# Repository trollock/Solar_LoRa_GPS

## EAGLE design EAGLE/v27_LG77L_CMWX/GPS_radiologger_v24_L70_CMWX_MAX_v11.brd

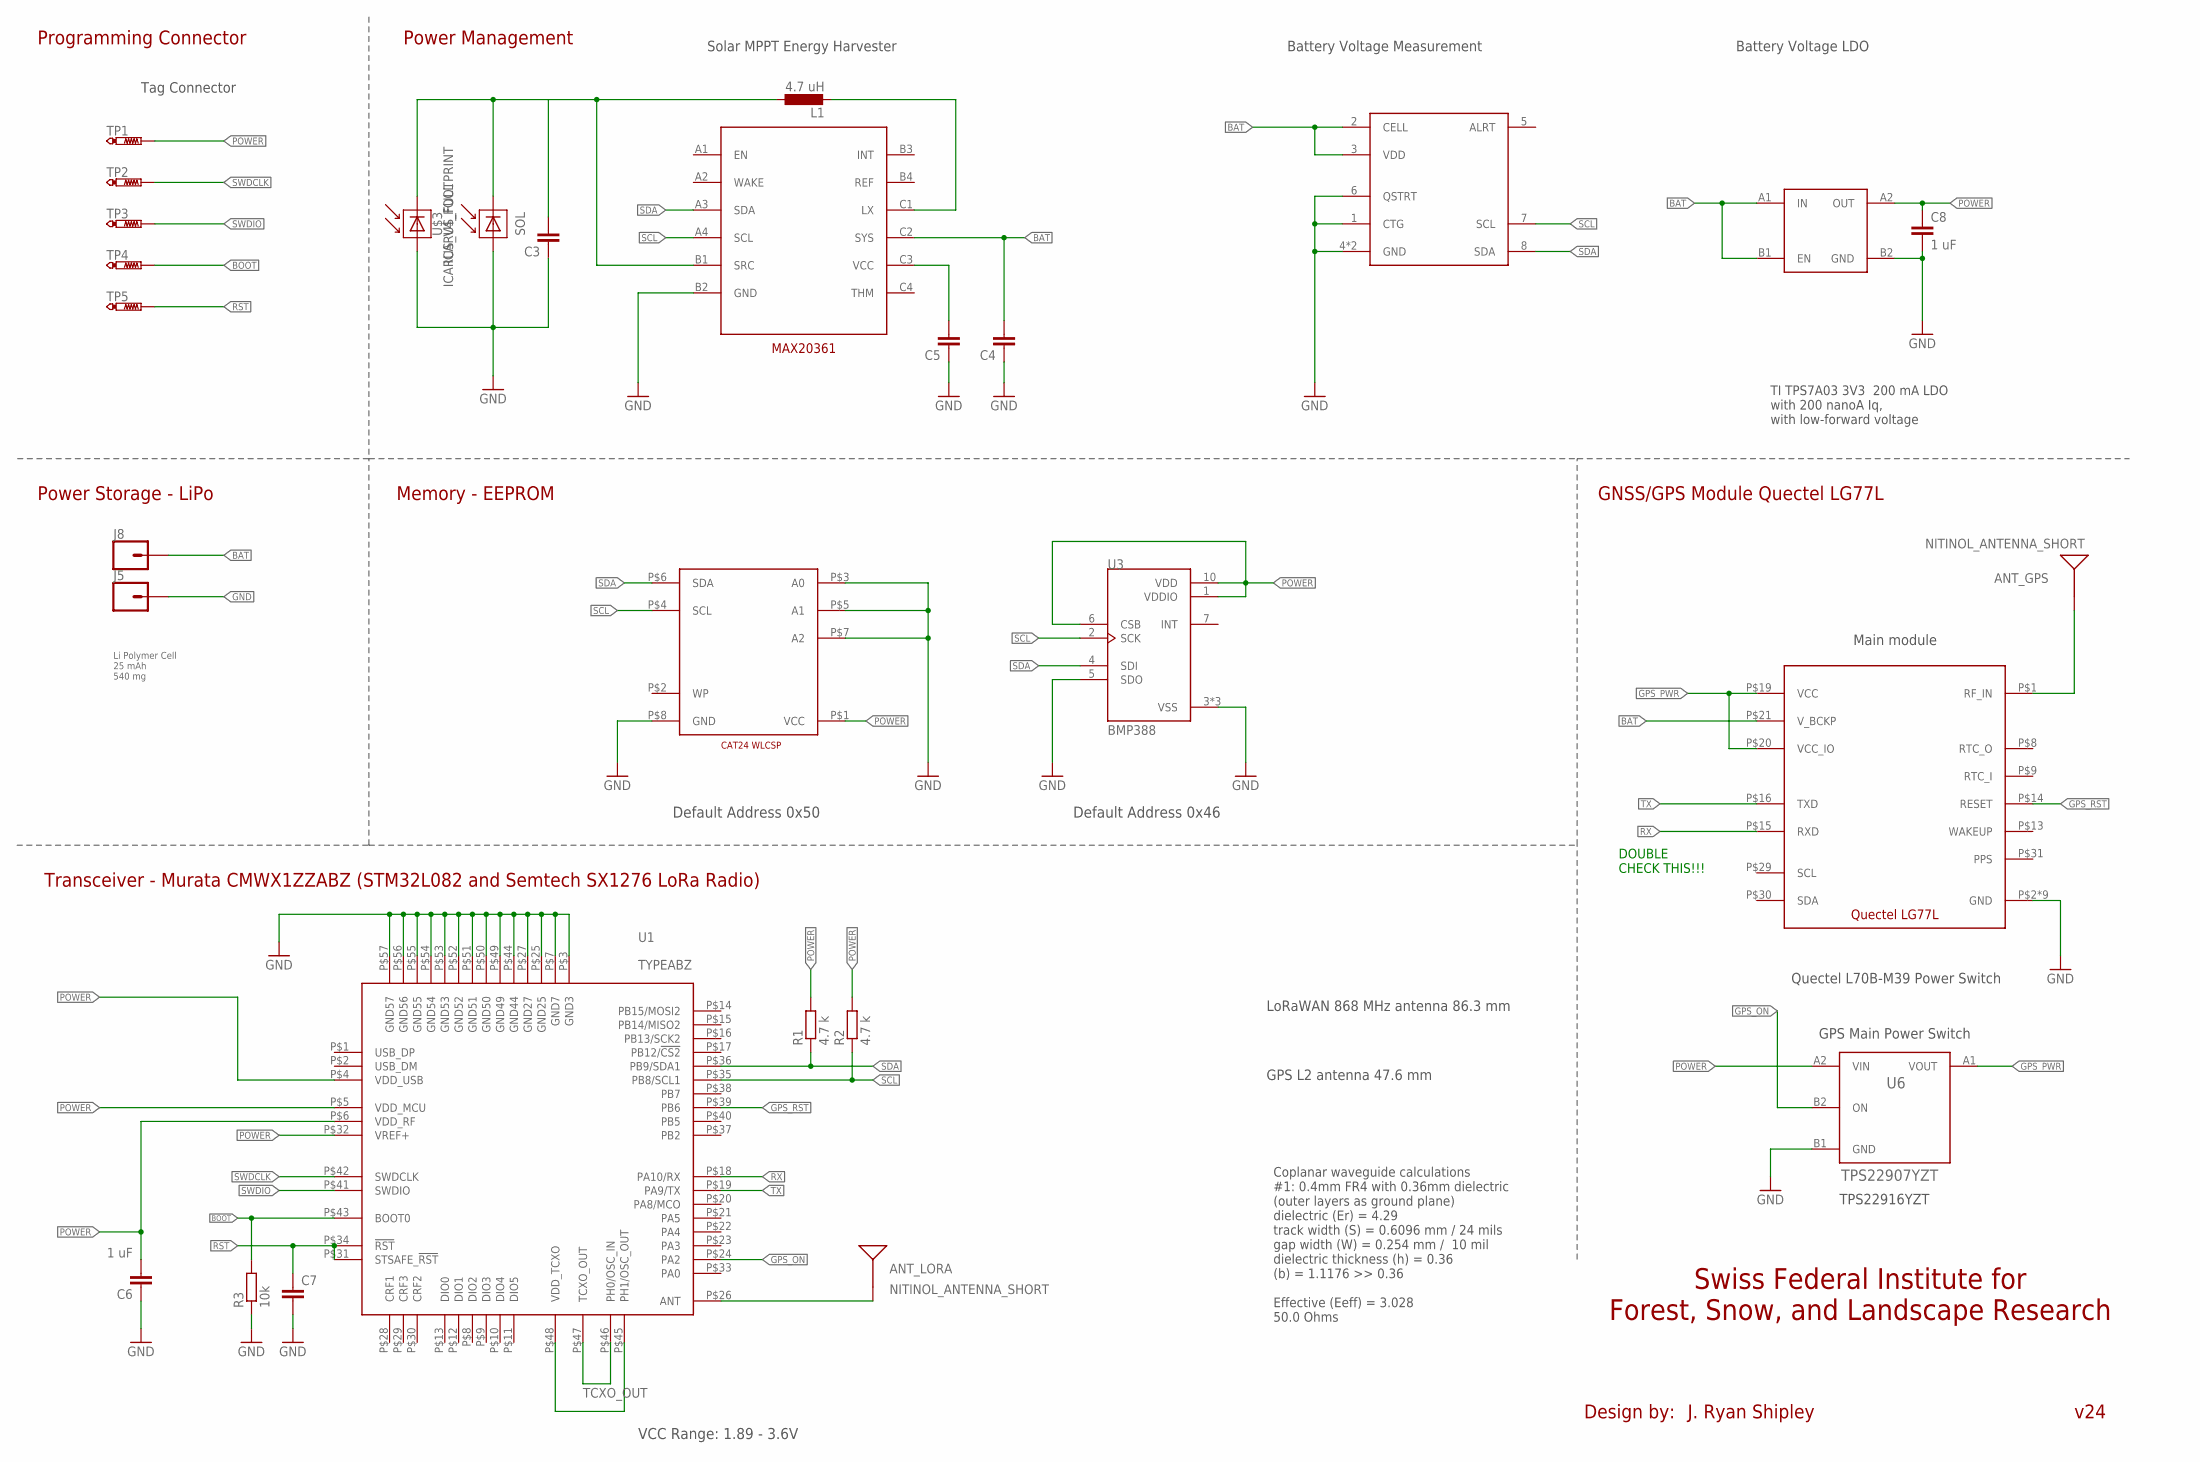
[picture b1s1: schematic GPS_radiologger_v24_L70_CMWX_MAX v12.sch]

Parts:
ANT_GPS: NITINOL_ANTENNA_SHORT; ICARUS_NITINOL_ANTENNA_SHORT
ANT_LORA: NITINOL_ANTENNA_SHORT; ICARUS_NITINOL_ANTENNA_SHORT
C3: 10UF; 0603-TIGHT
C4, C5: 1.0UF; 0402-TIGHTER
C6, C8: 1 uF; 0402-TIGHTER
C7: C-EUC0201; C0201
J5, J8: CONN_01PTH_NO_SILK_SMALL; 1X01_SMALL
L1: 4.7 uH; INDC2016X120L
R1, R2: 4.7 k; R0201
R3: 10k; R0201
SOL: ICARUS_V4_FOOTPRINT; ICARUS_FULL_FOOTPRINT
TP1, TP2, TP3, TP4, TP5: PTR1TP08SQ; TP08SQ
U1: TYPEABZ
U2: LG77L
U3: BMP388; PQFN50P200X200X80-10N
U4: TPS7A03-DSBGA; BGA4N35P2X2_70X70X40N
U5: MAX17048G+; SON50P200X200X75-9T80X120L
U6: TPS22907YZT; YFP0004-DSBGA
U7: CAT24_WLCSP8; WLCSP8
U8: MAX20361; BGA12N40P4X3_123X163X64N
U$3: ICARUS_FULL

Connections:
BAT: C4.P$2 (2), J8.P$1, U2.P$21 (V_BCKP), U4.A1 (IN), U4.B1 (EN), U5.2 (CELL), U5.3 (VDD), U8.C2 (SYS); also elsewhere on the board
BOOT: R3.2, TP4.TP, U1.P$43 (BOOT0)
GND: C3.P$1 (1), C4.P$1 (1), C5.P$1 (1), C6.P$1 (1), C7.2, C8.P$2 (2), J5.P$1, R3.1, SOL.P$2 (MINUS), U1.P$3 (GND3), U1.P$7 (GND7), U1.P$25 (GND25), U1.P$27 (GND27), U1.P$44 (GND44), U1.P$49 (GND49), U1.P$50 (GND50), U1.P$51 (GND51), U1.P$52 (GND52), U1.P$53 (GND53), U1.P$54 (GND54), U1.P$55 (GND55), U1.P$56 (GND56), U1.P$57 (GND57), U2.P$2 (GND), U3.3 (VSS), U3.5 (SDO), U3.8 (VSS), U3.9 (VSS), U4.B2 (GND), U5.1 (CTG), U5.4 (GND), U5.6 (QSTRT), U6.B1 (GND), U7.P$3 (A0), U7.P$5 (A1), U7.P$7 (A2), U7.P$8 (GND), U8.B2 (GND), U$3.P$2 (MINUS); also elsewhere on the board
GPS_ON: U1.P$24 (PA2), U6.B2 (ON)
GPS_PWR: U2.P$19 (VCC), U2.P$20 (VCC_IO), U6.A1 (VOUT); also elsewhere on the board
GPS_RST: U1.P$39 (PB6), U2.P$14 (RESET); also elsewhere on the board
unnamed: U1.P$45 (PH1/OSC_OUT), U1.P$48 (VDD_TCXO)
unnamed 7: ANT_GPS.1, ANT_GPS.2, ANT_GPS.3, U2.P$1 (RF_IN); also elsewhere on the board
unnamed: L1.2, U8.C1 (LX)
unnamed: C5.P$2 (2), U8.C3 (VCC)
unnamed: ANT_LORA.1, ANT_LORA.2, ANT_LORA.3, U1.P$26 (ANT)
unnamed: C3.P$2 (2), L1.1, SOL.P$1 (PLUS), U8.B1 (SRC), U$3.P$1 (PLUS)
POWER: C6.P$2 (2), C8.P$1 (1), R1.2, R2.2, TP1.TP, U1.P$4 (VDD_USB), U1.P$5 (VDD_MCU), U1.P$6 (VDD_RF), U1.P$32 (VREF+), U3.1 (VDDIO), U3.6 (CSB), U3.10 (VDD), U4.A2 (OUT), U6.A2 (VIN), U7.P$1 (VCC)
RST: C7.1, TP5.TP, U1.P$31 (STSAFE_!RST), U1.P$34 (!RST)
RX: U1.P$18 (PA10/RX), U2.P$15 (RXD); also elsewhere on the board
SCL: R2.1, U1.P$35 (PB8/SCL1), U3.2 (SCK), U5.7 (SCL), U7.P$4 (SCL), U8.A4 (SCL); also elsewhere on the board
SDA: R1.1, U1.P$36 (PB9/SDA1), U3.4 (SDI), U5.8 (SDA), U7.P$6 (SDA), U8.A3 (SDA); also elsewhere on the board
SWDCLK: TP2.TP, U1.P$42 (SWDCLK)
SWDIO: TP3.TP, U1.P$41 (SWDIO)
TCXO_OUT: U1.P$46 (PH0/OSC_IN), U1.P$47 (TCXO_OUT)
TX: U1.P$19 (PA9/TX), U2.P$16 (TXD); also elsewhere on the board

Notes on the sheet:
GNSS/GPS Module Quectel LG77L
VCC Range: 1.89 - 3.6V
Swiss Federal Institute for Forest, Snow, and Landscape Research
Transceiver - Murata CMWX1ZZABZ (STM32L082 and Semtech SX1276 LoRa Radio)
Programming Connector
Power Storage - LiPo
Design by:
J. Ryan Shipley
v24
Li Polymer Cell 25 mAh 540 mg
Power Management
Solar MPPT Energy Harvester
Memory - EEPROM
Main module
Coplanar waveguide calculations #1: 0.4mm FR4 with 0.36mm dielectric (outer layers as ground plane) dielectric (Er) = 4.29 track width (S) = 0.6096 mm / 24 mils gap width (W) = 0.254 mm / 10 mil dielectric thickness (h) = 0.36 (b) = 1.1176 >> 0.36 Effective (Eeff) = 3.028 50.0 Ohms
Tag Connector
Default Address 0x50
GPS Main Power Switch
TI TPS7A03 3V3 200 mA LDO with 200 nanoA Iq, with low-forward voltage
Quectel L70B-M39 Power Switch
Battery Voltage Measurement
Battery Voltage LDO
Default Address 0x46
TPS22916YZT
GPS L2 antenna 47.6 mm
LoRaWAN 868 MHz antenna 86.3 mm
DOUBLE CHECK THIS!!!

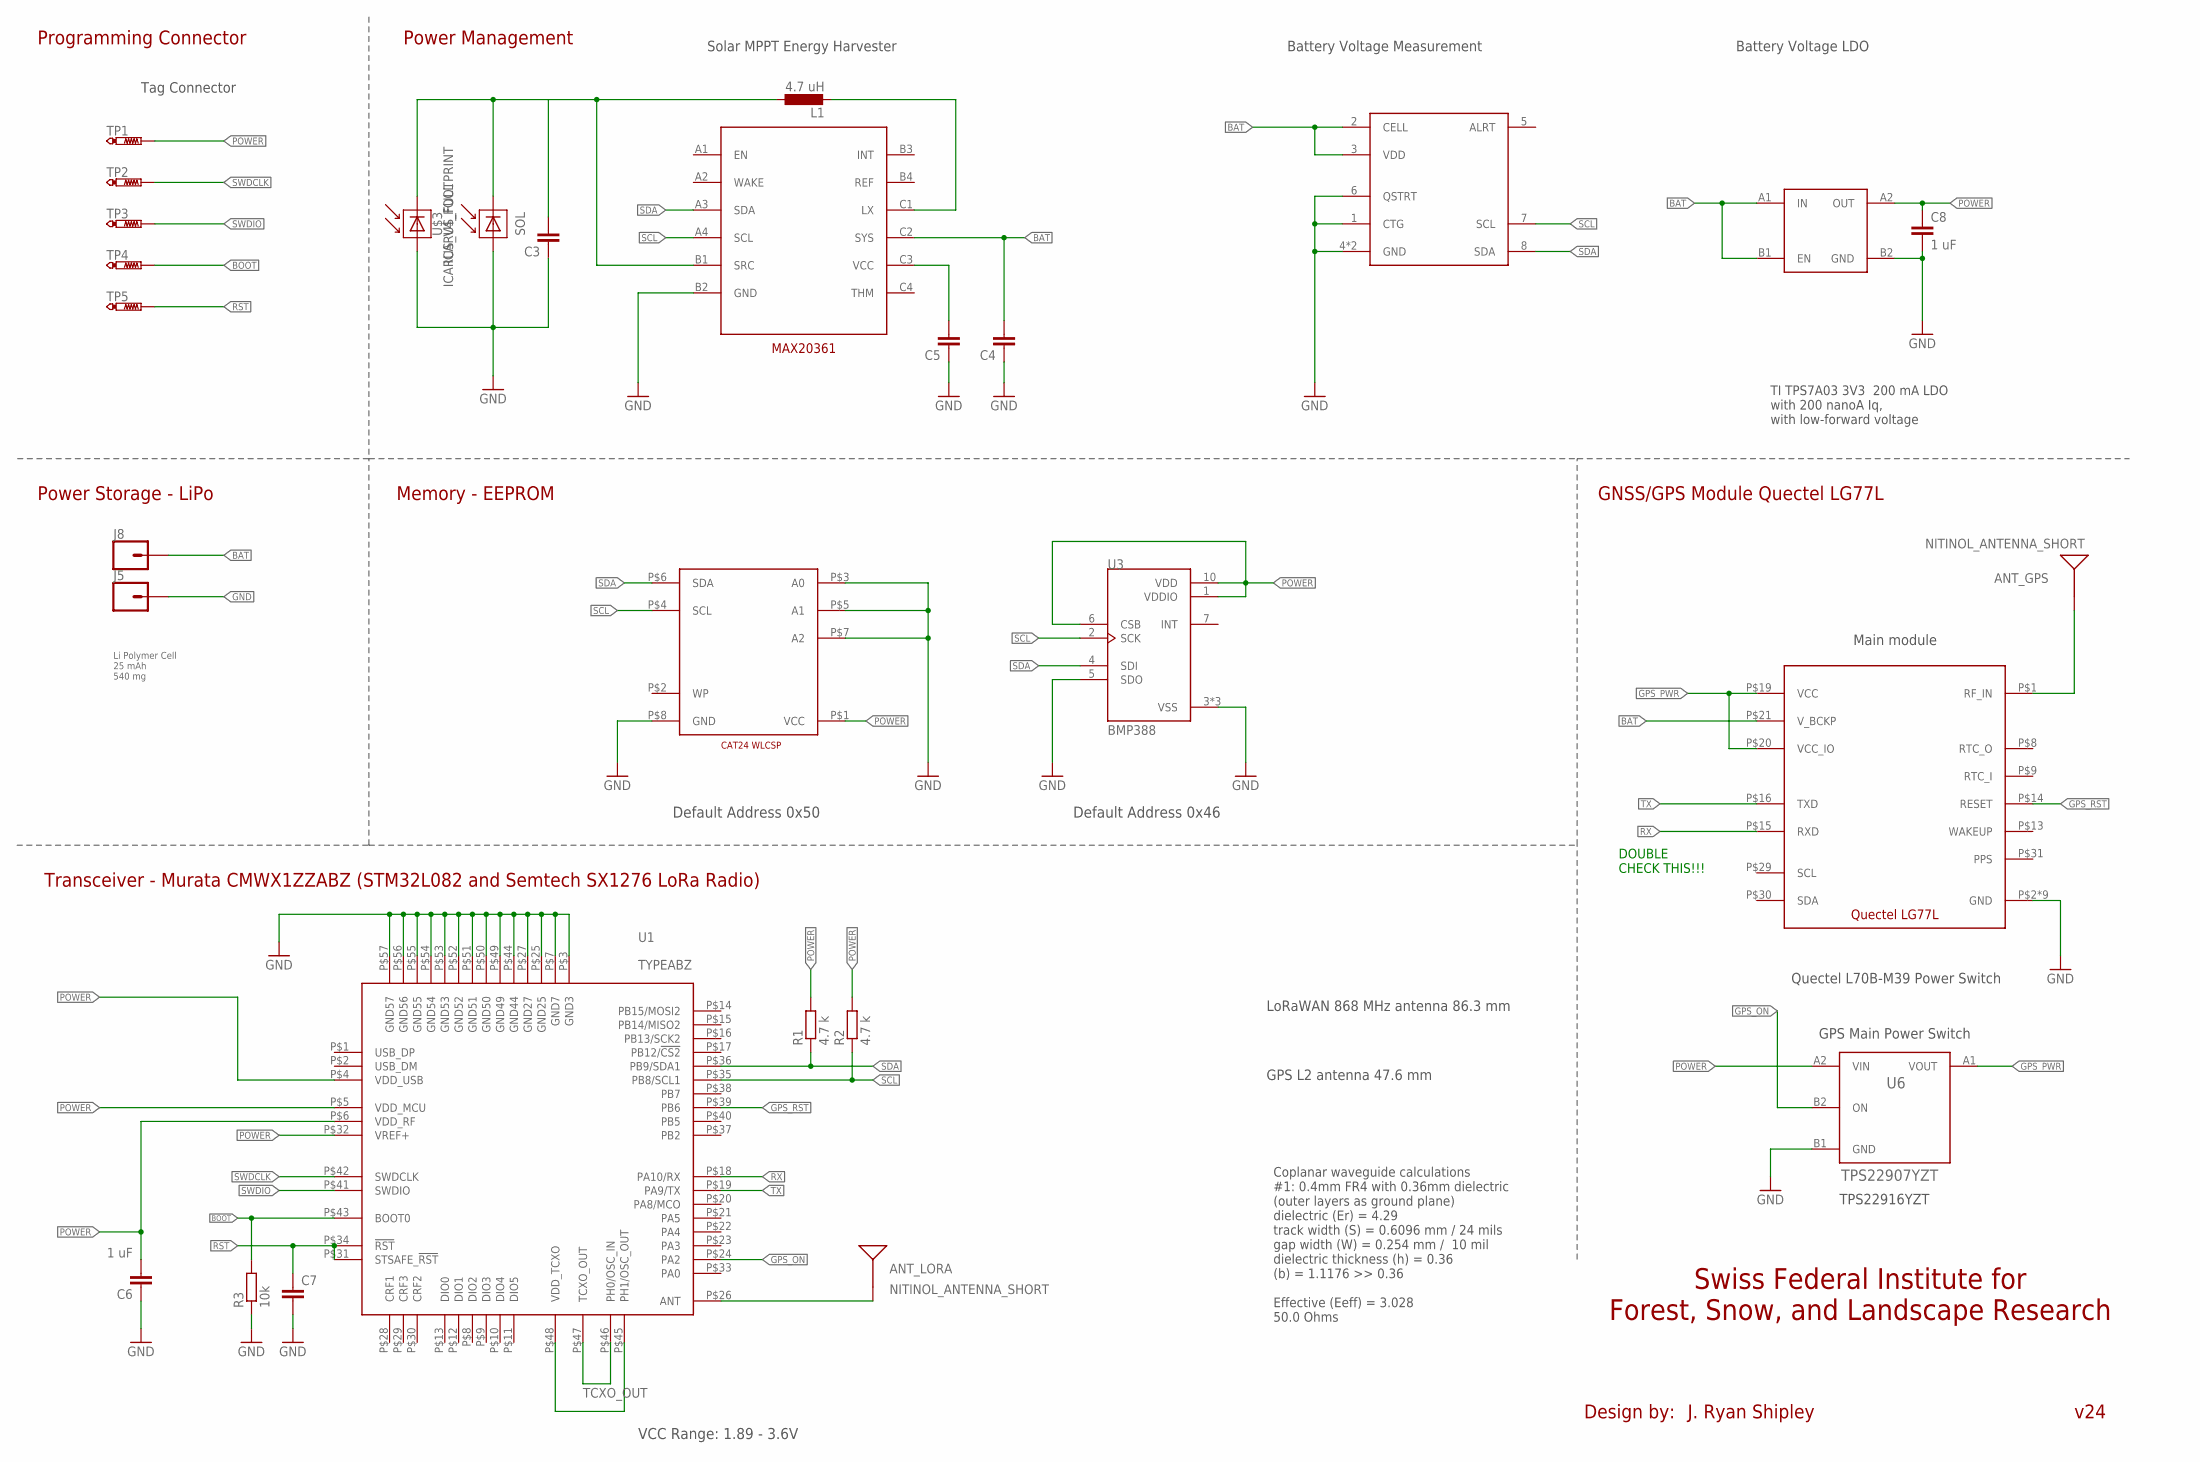
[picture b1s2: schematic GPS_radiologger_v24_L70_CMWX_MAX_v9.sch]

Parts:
ANT_GPS: NITINOL_ANTENNA_SHORT; ICARUS_NITINOL_ANTENNA_SHORT
ANT_LORA: NITINOL_ANTENNA_SHORT; ICARUS_NITINOL_ANTENNA_SHORT
C3: 10UF; 0603-TIGHT
C4, C5: 1.0UF; 0402-TIGHTER
C6, C8: 1 uF; 0402-TIGHTER
C7: C-EUC0201; C0201
J5, J8: CONN_01PTH_NO_SILK_SMALL; 1X01_SMALL
L1: 4.7 uH; INDC2016X120L
R1, R2: 4.7 k; R0201
R3: 10k; R0201
SOL: ICARUS_V4_FOOTPRINT; ICARUS_FULL_FOOTPRINT
TP1, TP2, TP3, TP4, TP5: PTR1TP08SQ; TP08SQ
U1: TYPEABZ
U3: BMP388; PQFN50P200X200X80-10N
U4: TPS7A03-DSBGA; BGA4N35P2X2_70X70X40N
U6: TPS22907YZT; YFP0004-DSBGA
U7: CAT24_WLCSP8; WLCSP8
U8: MAX20361; BGA12N40P4X3_123X163X64N
U$1: LG77L
U$2: MAX17048G+; SON50P200X200X75-9T80X120L
U$3: ICARUS_FULL

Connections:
BAT: C4.P$2 (2), J8.P$1, U4.A1 (IN), U4.B1 (EN), U8.C2 (SYS), U$1.P$21 (V_BCKP), U$2.2 (CELL), U$2.3 (VDD); also elsewhere on the board
BOOT: R3.2, TP4.TP, U1.P$43 (BOOT0)
GND: C3.P$1 (1), C4.P$1 (1), C5.P$1 (1), C6.P$1 (1), C7.2, C8.P$2 (2), J5.P$1, R3.1, SOL.P$2 (MINUS), U1.P$3 (GND3), U1.P$7 (GND7), U1.P$25 (GND25), U1.P$27 (GND27), U1.P$44 (GND44), U1.P$49 (GND49), U1.P$50 (GND50), U1.P$51 (GND51), U1.P$52 (GND52), U1.P$53 (GND53), U1.P$54 (GND54), U1.P$55 (GND55), U1.P$56 (GND56), U1.P$57 (GND57), U3.3 (VSS), U3.5 (SDO), U3.8 (VSS), U3.9 (VSS), U4.B2 (GND), U6.B1 (GND), U7.P$3 (A0), U7.P$5 (A1), U7.P$7 (A2), U7.P$8 (GND), U8.B2 (GND), U$1.P$2 (GND), U$1.P$18 (GND), U$1.P$37 (GND), U$1.P$38 (GND), U$1.P$39 (GND), U$1.P$40 (GND), U$1.P$41 (GND), U$1.P$42 (GND), U$1.P$43 (GND), U$2.1 (CTG), U$2.4 (GND), U$2.6 (QSTRT), U$2.9 (GND), U$3.P$2 (MINUS); also elsewhere on the board
GPS_ON: U1.P$24 (PA2), U6.B2 (ON)
GPS_PWR: U6.A1 (VOUT), U$1.P$19 (VCC), U$1.P$20 (VCC_IO); also elsewhere on the board
GPS_RST: U1.P$39 (PB6), U$1.P$14 (RESET); also elsewhere on the board
unnamed: U1.P$45 (PH1/OSC_OUT), U1.P$48 (VDD_TCXO)
unnamed 7: ANT_GPS.1, ANT_GPS.2, ANT_GPS.3, U$1.P$1 (RF_IN); also elsewhere on the board
unnamed: L1.2, U8.C1 (LX)
unnamed: C5.P$2 (2), U8.C3 (VCC)
unnamed: ANT_LORA.1, ANT_LORA.2, ANT_LORA.3, U1.P$26 (ANT)
unnamed: C3.P$2 (2), L1.1, SOL.P$1 (PLUS), U8.B1 (SRC), U$3.P$1 (PLUS)
POWER: C6.P$2 (2), C8.P$1 (1), R1.2, R2.2, TP1.TP, U1.P$4 (VDD_USB), U1.P$5 (VDD_MCU), U1.P$6 (VDD_RF), U1.P$32 (VREF+), U3.1 (VDDIO), U3.6 (CSB), U3.10 (VDD), U4.A2 (OUT), U6.A2 (VIN), U7.P$1 (VCC)
RST: C7.1, TP5.TP, U1.P$31 (STSAFE_!RST), U1.P$34 (!RST)
RX: U1.P$18 (PA10/RX), U$1.P$15 (RXD); also elsewhere on the board
SCL: R2.1, U1.P$35 (PB8/SCL1), U3.2 (SCK), U7.P$4 (SCL), U8.A4 (SCL), U$2.7 (SCL); also elsewhere on the board
SDA: R1.1, U1.P$36 (PB9/SDA1), U3.4 (SDI), U7.P$6 (SDA), U8.A3 (SDA), U$2.8 (SDA); also elsewhere on the board
SWDCLK: TP2.TP, U1.P$42 (SWDCLK)
SWDIO: TP3.TP, U1.P$41 (SWDIO)
TCXO_OUT: U1.P$46 (PH0/OSC_IN), U1.P$47 (TCXO_OUT)
TX: U1.P$19 (PA9/TX), U$1.P$16 (TXD); also elsewhere on the board

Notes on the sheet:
GNSS/GPS Module Quectel LG77L
VCC Range: 1.89 - 3.6V
Swiss Federal Institute for Forest, Snow, and Landscape Research
Transceiver - Murata CMWX1ZZABZ (STM32L082 and Semtech SX1276 LoRa Radio)
Programming Connector
Power Storage - LiPo
Design by:
J. Ryan Shipley
v24
Li Polymer Cell 25 mAh 540 mg
Power Management
Solar MPPT Energy Harvester
Memory - EEPROM
Main module
Coplanar waveguide calculations #1: 0.4mm FR4 with 0.36mm dielectric (outer layers as ground plane) dielectric (Er) = 4.29 track width (S) = 0.6096 mm / 24 mils gap width (W) = 0.254 mm / 10 mil dielectric thickness (h) = 0.36 (b) = 1.1176 >> 0.36 Effective (Eeff) = 3.028 50.0 Ohms
Tag Connector
Default Address 0x50
GPS Main Power Switch
TI TPS7A03 3V3 200 mA LDO with 200 nanoA Iq, with low-forward voltage
Quectel L70B-M39 Power Switch
Battery Voltage Measurement
Battery Voltage LDO
Default Address 0x46
TPS22916YZT
GPS L2 antenna 47.6 mm
LoRaWAN 868 MHz antenna 86.3 mm
DOUBLE CHECK THIS!!!

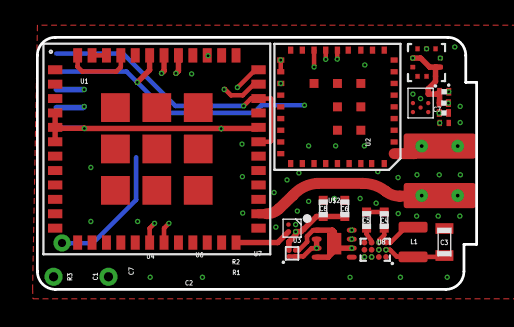
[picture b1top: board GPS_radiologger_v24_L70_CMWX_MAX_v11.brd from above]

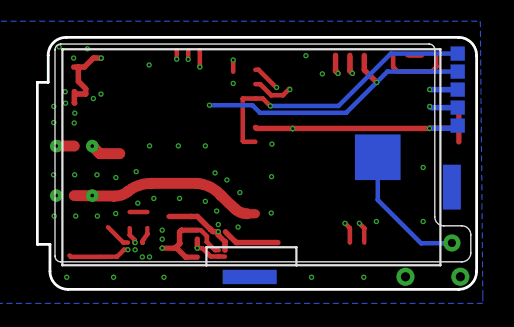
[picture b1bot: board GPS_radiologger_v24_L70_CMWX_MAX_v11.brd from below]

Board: 4 copper layers, 24.4 x 14.0 mm, 29 parts (8 on the bottom side), 21 nets.

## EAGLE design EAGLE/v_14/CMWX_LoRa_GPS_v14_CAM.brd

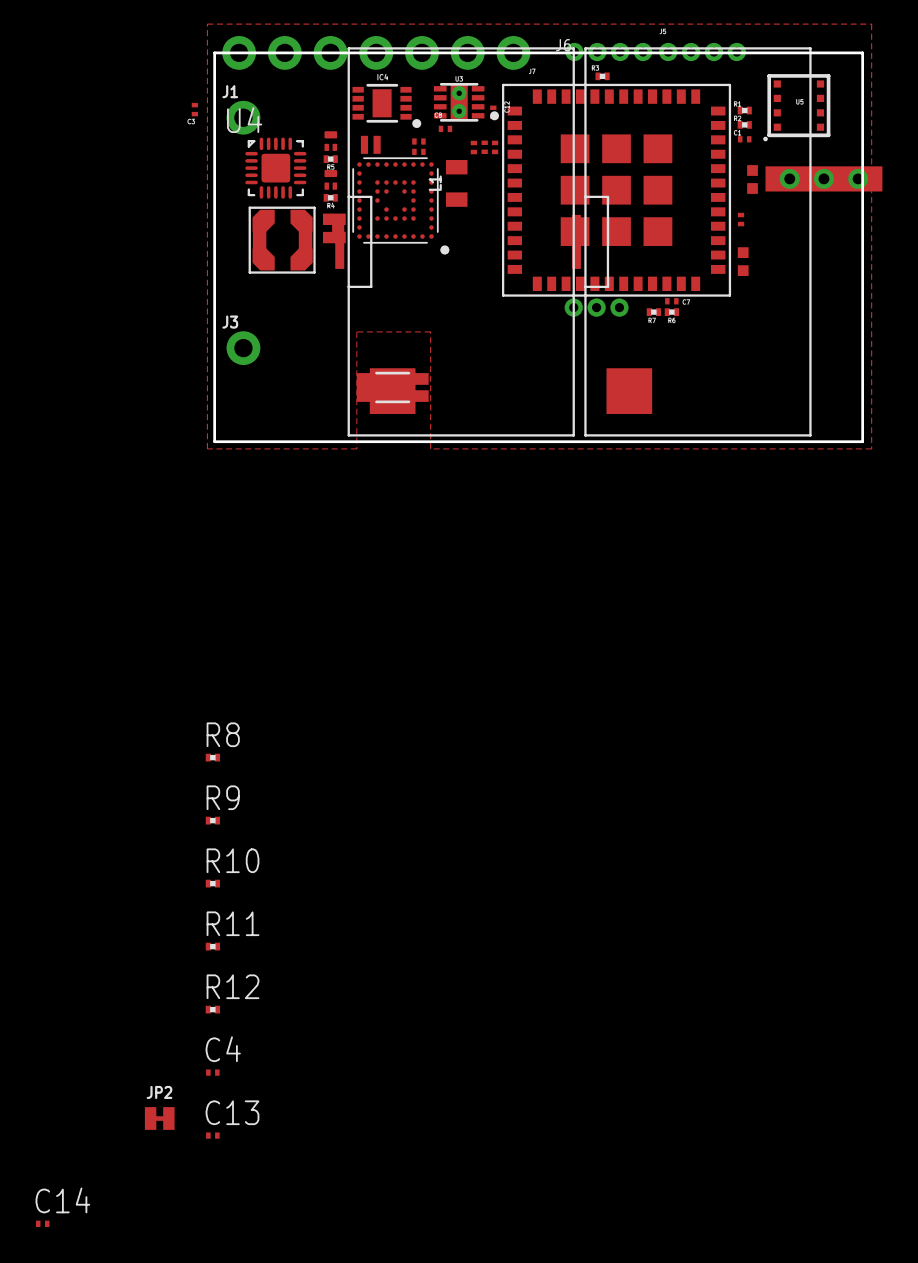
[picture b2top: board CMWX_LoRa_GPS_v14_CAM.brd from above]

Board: 4 copper layers, 36.0 x 21.6 mm, 51 parts (0 on the bottom side), 36 nets, no tracks yet.

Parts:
C1, C3, C6, C7, C10, C11: 0.1 uF; C0201
C2, C12: 10 uF; C0201
C4: 10nF; C0201
C5, C8, C14: 4.7 uF; C0201
C9: 1 uF; C0201
C13: 47uF; C0201
IC4: CAT24M01HU5I-GT3; SON50P300X200X55-9N
J1, J3: 1X01_NO_SILK
J4: 1X03_1.27MM_NO_SILK
J5, J6: 1X04_1.27MM_NO_SILK
J7: 1X07_NO_SILK
JP1, JP2: JUMPER-SMT_2_NC_TRACE_NO-SILK; SMT-JUMPER_2_NC_TRACE_NO-SILK
L1: 2.2µH/< 0.2 ohm /500mA; 0805
L3, L4: FERRITE_BEAD-120_OHM_TIGHT; 0402-TIGHT
PDTA143TMB,1, PDTA143TMB,315: TINYPICO-PNPAMB; SOT883(B)
R1, R2: 4.7 k; R0201
R3: 10k; R0201
R4, R5: 100k; R0201
R6: 10 M; R0201
R7: 4.7 M; R0201
R8, R12: 3M; R0201
R9: 9.1M; R0201
R10: 6.2M; R0201
R11: 1M; R0201
U1: TYPEABZ
U2: UBLOX_ZOE_M8-0-10
U3: MICROCHIP_MCP1810T-33I-J8AMICROCHIP_MCP1810T-33I-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; MICROCHIP_MCP1810T-33I-J8A_0
U4: SPV1050
U5: BME680BME680; LGA3.0X3.0
U$1: LPS3015; LPS_3015
U$2: NITINOL_ANTENNA; ICARUS_NITINOL_ANTENNA
U$3, U$4: ICARUS_FULL
Y1: 32.768kHz; CRYSTAL-SMD-1.0X1.2MM
Y2: W3011

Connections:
ANT: C11.1, L4.1, U$2.P$1, U$2.P$2, U$2.P$3, U$2.P$4
BAT: C8.1, J1.1, JP2.2, R7.2, U3.7, U3.8
BOOT: J5.1, R3.2, U1.P$43
DM: J6.2, U1.P$2
DP: J6.3, U1.P$1
GND: C1.2, C2.1, C3.2, C4.2, C5.2, C6.2, C7.2, C8.2, C9.1, C10.1, C12.2, C13.2, C14.2, IC4.4, IC4.9, J3.1, J6.4, J7.1, J7.6, L3.2, L4.2, R3.1, R6.1, R9.1, R12.1, U1.P$3, U1.P$7, U1.P$25, U1.P$27, U1.P$44, U1.P$49, U1.P$50, U1.P$51, U1.P$52, U1.P$53, U1.P$54, U1.P$55, U1.P$56, U1.P$57, U2.1, U2.3, U2.5, U2.7, U2.8, U2.9, U2.10, U2.11, U2.12, U2.17, U2.23, U2.29, U2.31, U2.37, U2.38, U2.39, U2.40, U2.41, U2.44, U2.46, U2.47, U2.49, U3.1, U3.9, U4.P$4, U4.P$5, U4.P$6, U4.P$18, U4.P$19, U4.P$20, U4.P$21, U5.1, U5.5, U5.7, U$3.P$2, Y2.2, Y2.3
GPS_ANT: U2.4, Y2.1
unnamed: U1.P$45, U1.P$48
unnamed: JP1.2, U2.16
unnamed: C5.1, L1.1, U2.27
unnamed: U4.P$16, U$1.P$2
unnamed: L1.2, U2.26
unnamed: R8.1, R9.2, U4.P$2
unnamed: R10.1, R11.2, U4.P$10
unnamed: R11.1, R12.2, U4.P$9
unnamed: JP2.1, U4.P$14
unnamed: C14.1, R8.2, U4.P$1, U4.P$13, U$1.P$1, U$3.P$1
unnamed: C13.1, R10.2, U4.P$15
unnamed: C4.1, U4.P$3
unnamed: U2.18, Y1.P$2
unnamed: U2.19, Y1.P$1
unnamed: C11.2, L3.1, U1.P$26
POWER: C2.2, C3.1, C6.1, C9.2, C10.2, C12.1, IC4.8, J4.1, JP1.1, PDTA143TMB,1.2, PDTA143TMB,315.2, R1.2, R2.2, R4.2, R5.2, U1.P$4, U1.P$5, U1.P$6, U1.P$32, U2.24, U2.25, U3.2, U3.6, U5.6, U5.8
RST: C1.1, J5.4, U1.P$34
RX: J4.2, U1.P$18
SCD_PDTA: PDTA143TMB,1.1, R5.1, U1.P$23
SCD_PWR: J7.7, PDTA143TMB,1.3
SCL: IC4.6, J7.5, R2.1, U1.P$35, U2.32, U5.4
SDA: IC4.5, J7.4, R1.1, U1.P$36, U2.2, U5.3
SWDCLK: J5.2, U1.P$42
SWDIO: J5.3, U1.P$41
TCXO_OUT: U1.P$46, U1.P$47
TX: J4.3, U1.P$19
VBUS: J6.1, U1.P$20
VOLT_MEAS: C7.1, R6.2, R7.1, U1.P$22
ZOE_PDTA: PDTA143TMB,315.1, R4.1, U1.P$24

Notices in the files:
parts and their libraries:
SparkFun-Aesthetics: Licensing: Creative Commons ShareAlike 4.0 International - https://creativecommons.org/licenses/by-sa/4.0
